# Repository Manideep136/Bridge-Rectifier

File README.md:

# Bridge-Rectifier

📌 Project Overview

This project is a Bridge Rectifier PCB designed using KiCad. The circuit converts an AC input voltage into DC output voltage using four diodes connected in a bridge configuration.

A bridge rectifier is one of the most commonly used circuits in power supplies because it uses both the positive and negative half cycles of the AC input to produce a pulsating DC output.

The PCB was designed in KiCad, including the schematic, footprint assignment, PCB layout, routing, and 3D visualization.

🎯 Objectives
Design a bridge rectifier circuit.
Convert AC voltage into DC voltage.
Understand the working of four-diode bridge rectification.
Design the schematic in KiCad.
Assign appropriate footprints to components.
Create and route the PCB.
Perform ERC and DRC checks.
Visualize the final PCB using KiCad 3D Viewer.
⚙️ Working Principle

The bridge rectifier consists of four diodes (D1, D2, D3, and D4) connected in a bridge arrangement.

During the positive half cycle of the AC input, two diodes conduct and current flows through the load in one direction.

During the negative half cycle, the other two diodes conduct. Even though the AC input polarity reverses, the current through the load continues in the same direction.

Therefore, both halves of the AC waveform are converted into a pulsating DC waveform.

Basic Operation
              + DC
                │
                │
           ┌────┴────┐
           │         │
          D1         D2
           │         │
 AC IN ~ ──┤         ├── ~ AC IN
           │         │
          D3         D4
           │         │
           └────┬────┘
                │
              - DC
🔌 Input and Output
AC Input

The AC input is connected to the two terminals marked:

AC ~
AC ~
DC Output

The rectified output is available at:

+ DC
- DC

The output can be connected to a load or a filter capacitor depending on the application.

🧩 Components Used
Reference	Component	Quantity
D1	Rectifier Diode	1
D2	Rectifier Diode	1
D3	Rectifier Diode	1
D4	Rectifier Diode	1
J1	AC Input Connector	1
J2	DC Output Connector	1

The exact diode part number and connector type depend on the physical components selected for the PCB.

📐 PCB Design

The PCB was designed using KiCad.

The design workflow was:

Create the bridge rectifier schematic.
Add the four rectifier diodes.
Add AC input and DC output connectors.
Connect all components according to the bridge rectifier circuit.
Assign footprints.
Transfer the schematic to PCB Editor.
Arrange the components.
Route the PCB tracks.
Check clearances and connections.
Run ERC and DRC.
Inspect the PCB using the 3D Viewer.
🖥️ KiCad Files

The project contains the following main files:

Bridge-Rectifier/
│
├── Bridge-Rectifier.kicad_pro
├── Bridge-Rectifier.kicad_sch
├── Bridge-Rectifier.kicad_pcb
├── README.md
│
└── Images/
    ├── schematic.png
    ├── pcb_layout.png
    └── 3d_view.png
File Description
File	Description
.kicad_pro	KiCad project configuration
.kicad_sch	Circuit schematic
.kicad_pcb	PCB layout and routing
README.md	Project documentation
Images/	Schematic, PCB and 3D-view images
🔄 Rectification Process

The AC waveform contains both positive and negative half cycles.

AC Input
       / \       / \
      /   \     /   \
-----/-----\---/-----\-----
    /       \ /       \
Bridge Rectifier Output

After rectification, both halves appear in the same direction:

       / \       / \
      /   \     /   \
-----/-----\---/-----\-----

The negative half cycle is flipped to the positive side.

The resulting waveform is called full-wave pulsating DC.

🔋 Adding a Filter Capacitor

A capacitor can be connected across the DC output to reduce ripple.

          + DC
            │
            ├───────┐
            │       │
           C1      LOAD
            │       │
            └───────┘
            │
          - DC

The capacitor charges when the rectified voltage increases and discharges through the load when the voltage decreases.

This produces a smoother DC output.

📊 Advantages
Uses both half cycles of the AC input.
Higher efficiency compared with a half-wave rectifier.
Produces a higher average DC output.
Lower ripple frequency is easier to filter.
Simple and reliable circuit.
Widely used in DC power supplies.
⚠️ Important Considerations

Before manufacturing or powering the PCB:

Check the diode voltage rating.
Check the diode current rating.
Verify diode orientation.
Use connectors suitable for the expected current.
If using an electrolytic capacitor, verify its polarity.
Ensure the capacitor voltage rating is higher than the maximum expected DC voltage.
Verify PCB track width for the expected current.
⚠️ Safety

Do not connect this beginner PCB directly to 230 V AC mains.

For testing, use a safe, isolated, low-voltage AC source, such as the secondary side of an appropriately rated transformer.

If the PCB is ever intended for mains voltage, the design must include appropriate creepage/clearance, insulation, fusing, enclosure, connector ratings, and other safety requirements.

🧪 Testing Procedure
Inspect the PCB for solder bridges and incorrect connections.
Check the orientation of all four diodes.
Check the AC input terminals.
Check the positive and negative DC output terminals.
Verify the PCB tracks using the KiCad schematic.
Use a multimeter to check for unintended shorts.
Apply a safe low-voltage AC input.
Measure the DC voltage at the output.
If a capacitor is installed, check its polarity and voltage rating.
✅ KiCad Checks

Before manufacturing the PCB:

ERC – Electrical Rules Check

Run ERC in the schematic editor to identify problems such as:

Unconnected pins
Incorrect connections
Power-related warnings
Missing connections
DRC – Design Rules Check

Run DRC in the PCB Editor to check:

Track clearance
Unconnected nets
Track width
Copper spacing
Board-edge clearance
Other PCB design-rule violations
🚀 Future Improvements

This bridge rectifier PCB can be extended into a complete DC power supply by adding:

Filter capacitor
Voltage regulator such as 7805
LED power indicator
Fuse
Reverse-polarity protection
Screw terminals
Adjustable voltage regulator
Test points
Additional filtering
Example Power Supply
AC Input
   │
   ▼
Bridge Rectifier
   │
   ▼
Filter Capacitor
   │
   ▼
Voltage Regulator
   │
   ▼
Regulated DC Output
📚 Learning Outcomes

Through this project, I learned:

Working principle of a bridge rectifier.
AC-to-DC conversion.
Diode polarity and orientation.
Full-wave rectification.
Schematic creation in KiCad.
Footprint assignment.
PCB component placement.
PCB routing.
ERC and DRC.
KiCad 3D PCB visualization.
Basic PCB design practices.
🛠️ Software Used

KiCad 9.0

📄 License

This project is created for educational and learning purposes. You may modify and improve the design for your own electronics and PCB projects.

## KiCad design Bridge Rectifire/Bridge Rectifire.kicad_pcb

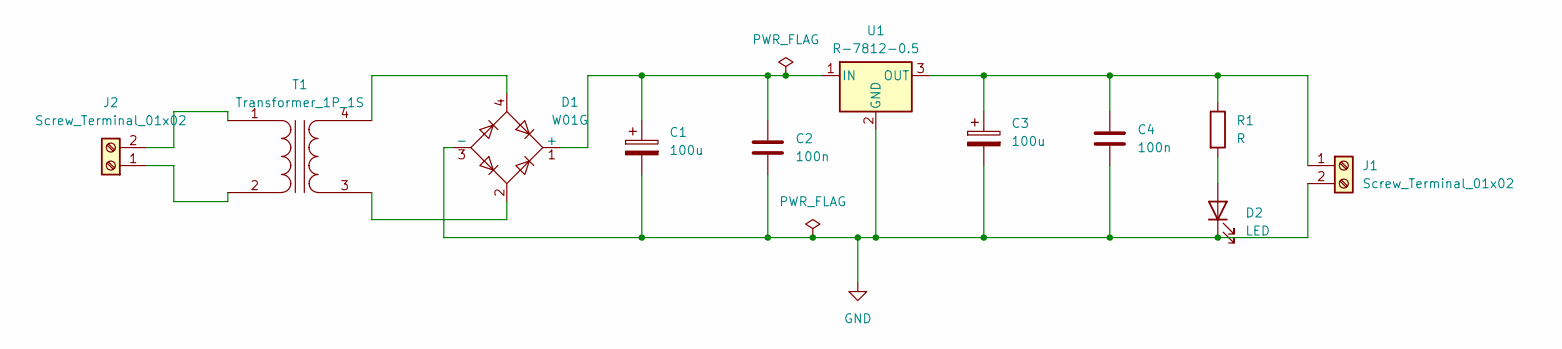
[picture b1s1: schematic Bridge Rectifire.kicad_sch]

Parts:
C1, C3: 100u; CP_Radial_D8.0mm_P3.80mm
C2, C4: 100n; CP_Radial_D8.0mm_P3.80mm
D1: W01G; Diode_Bridge_Round_D9.8mm
D2: LED; LED_D5.0mm
J1, J2: Screw_Terminal_01x02; TerminalBlock_Phoenix_MKDS-1,5-2-5.08_1x02_P5.08mm_Horizont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
R1: R; R_Axial_DIN0207_L6.3mm_D2.5mm_P7.62mm_Horizontal
T1: Transformer_1P_1S; Transformer_Zeming_ZMPT101K
U1: R-7812-0.5; Converter_DCDC_RECOM_R-78E-0.5_THT

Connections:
GND: C1.2, C2.2, C3.2, C4.2, D1.3 (-), D2.1 (K), J1.2, U1.2 (GND)
unnamed: C1.1, C2.1, D1.1 (+), U1.1 (IN)
unnamed: D2.2 (A), R1.2
unnamed: C3.1, C4.1, J1.1, R1.1, U1.3 (OUT)
unnamed: J2.1, T1.2 (AB)
unnamed: J2.2, T1.1 (AA)
unnamed: D1.2, T1.3 (SA)
unnamed: D1.4, T1.4 (SB)

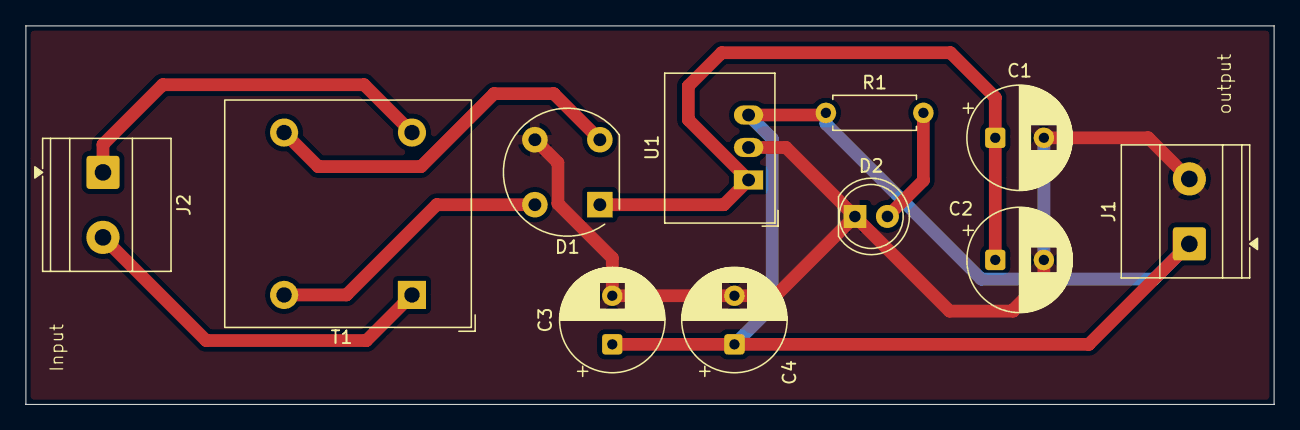
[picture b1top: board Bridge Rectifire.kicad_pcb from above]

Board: 2 copper layers, 97.6 x 29.6 mm, 11 parts (0 on the bottom side), 8 nets.
